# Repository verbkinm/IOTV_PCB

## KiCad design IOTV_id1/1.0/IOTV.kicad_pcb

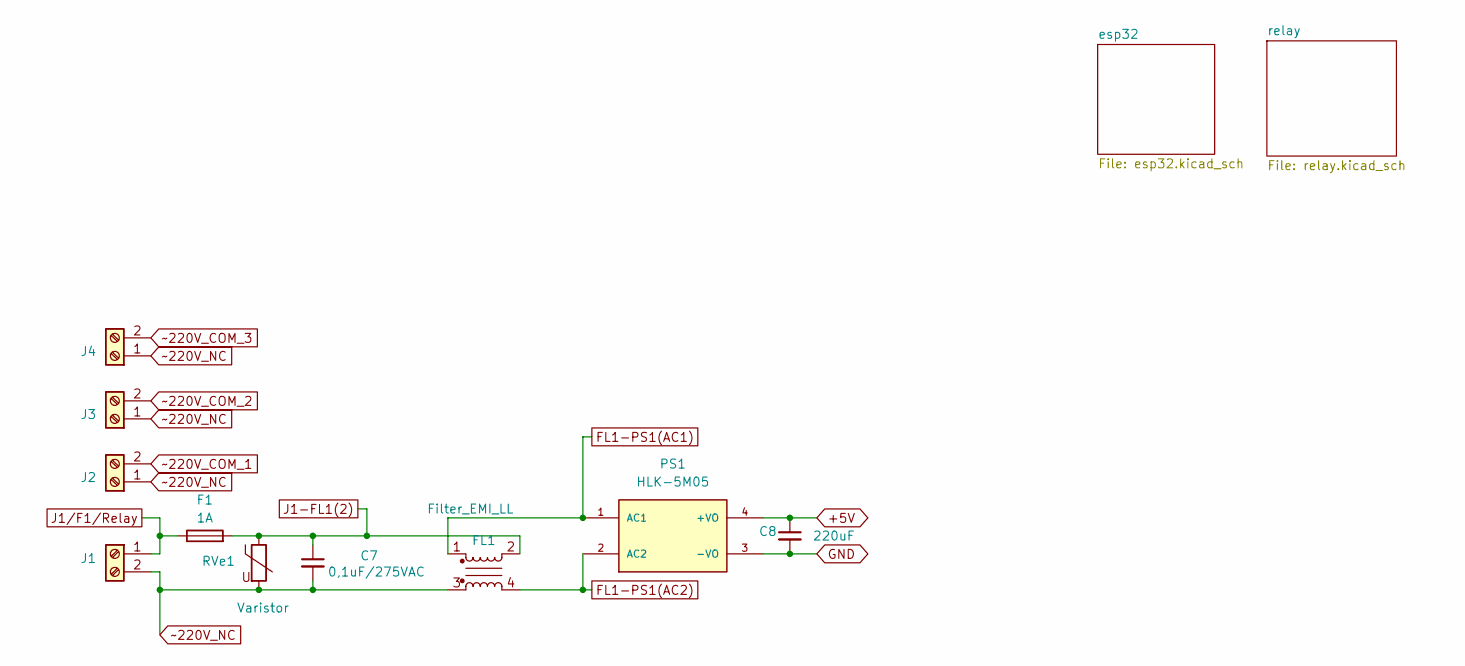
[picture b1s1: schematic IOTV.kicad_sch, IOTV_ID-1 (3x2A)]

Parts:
C7: C_Generic; C_Rect_L13.0mm_W5.0mm_P10.00mm_FKS3_FKP3_MKS4
C8: C_Generic; CP_Radial_D8.0mm_P5.00mm
F1: 1A; Fuseholder_Cylinder-5x20mm_Schurter_0031_8201_Horizontal_Op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
FL1: Filter_EMI_LL; L_CommonMode_Toroid_Vertical_10x13mm
J1, J2, J3, J4: Screw_Terminal_01x02; TerminalBlock_Phoenix_MKDS-1,5-2_1x02_P5.00mm_Horizontal
PS1: HLK-5M05; Converter_ACDC_Hi-Link_HLK-5Mxx; PARTREV N/A
RVe1: Varistor; RV_Disc_D21.5mm_W4.8mm_P10mm

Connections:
+5V: C8.1, PS1.4 (+VO); also elsewhere on the board
FL1-PS1(AC1): FL1.1, PS1.1 (AC1)
FL1-PS1(AC2): FL1.4, PS1.2 (AC2)
GND: C8.2, PS1.3 (-VO); also elsewhere on the board
J1-FL1(2): C7.1, F1.2, FL1.2, RVe1.1
J1/F1/Relay: F1.1, J1.1; also elsewhere on the board
~220V_COM_1: J2.2; also elsewhere on the board
~220V_COM_2: J3.2; also elsewhere on the board
~220V_COM_3: J4.2; also elsewhere on the board
~220V_NC: C7.2, FL1.3, J1.2, J2.1, J3.1, J4.1, RVe1.2

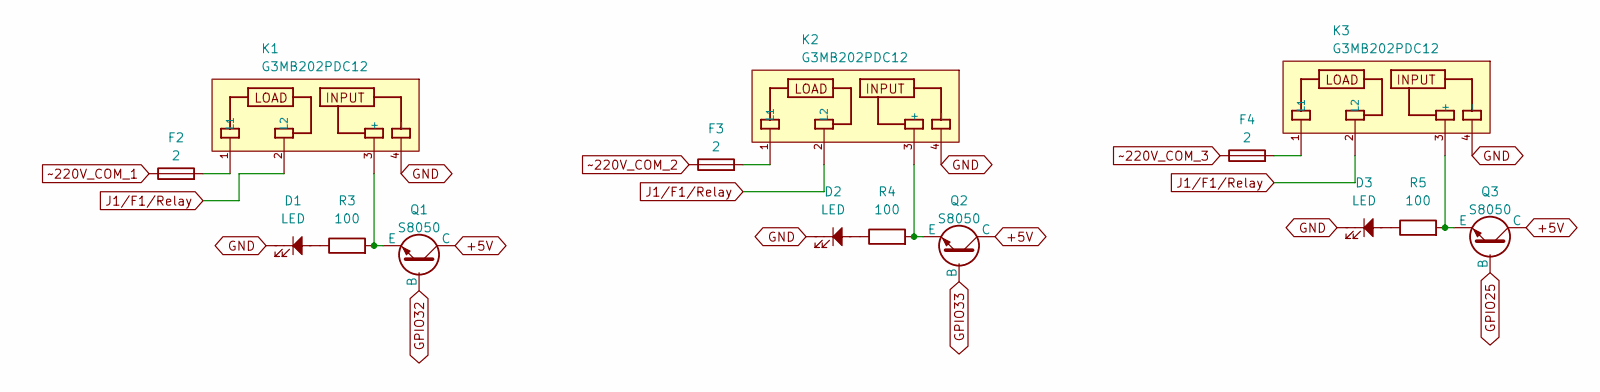
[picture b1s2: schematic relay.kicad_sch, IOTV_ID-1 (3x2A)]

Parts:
D1, D2, D3: LED; D_0603_1608Metric
F2, F3, F4: 2; Fuseholder_Cylinder-5x20mm_Schurter_0031_8201_Horizontal_Op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
K1, K2, K3: G3MB202PDC12; RELAY_G3MB202PDC12; PARTREV N/A
Q1, Q2, Q3: S8050; SOT-23
R3, R4, R5: 100; R_1206_3216Metric

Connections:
+5V: Q1.3 (C), Q2.3 (C), Q3.3 (C); also elsewhere on the board
GND: D1.1, D2.1, D3.1, K1.4 (-), K2.4 (-), K3.4 (-); also elsewhere on the board
GPIO25: Q3.1 (B); also elsewhere on the board
GPIO32: Q1.1 (B); also elsewhere on the board
GPIO33: Q2.1 (B); also elsewhere on the board
J1/F1/Relay: K1.2 (L2), K2.2 (L2), K3.2 (L2); also elsewhere on the board
unnamed: D1.2, R3.1
unnamed: D2.2, R4.1
unnamed: D3.2, R5.1
unnamed: K1.3 (+), Q1.2 (E), R3.2
unnamed: F2.2, K1.1 (L1)
unnamed: K2.3 (+), Q2.2 (E), R4.2
unnamed: F3.2, K2.1 (L1)
unnamed: K3.3 (+), Q3.2 (E), R5.2
unnamed: F4.2, K3.1 (L1)
~220V_COM_1: F2.1; also elsewhere on the board
~220V_COM_2: F3.1; also elsewhere on the board
~220V_COM_3: F4.1; also elsewhere on the board

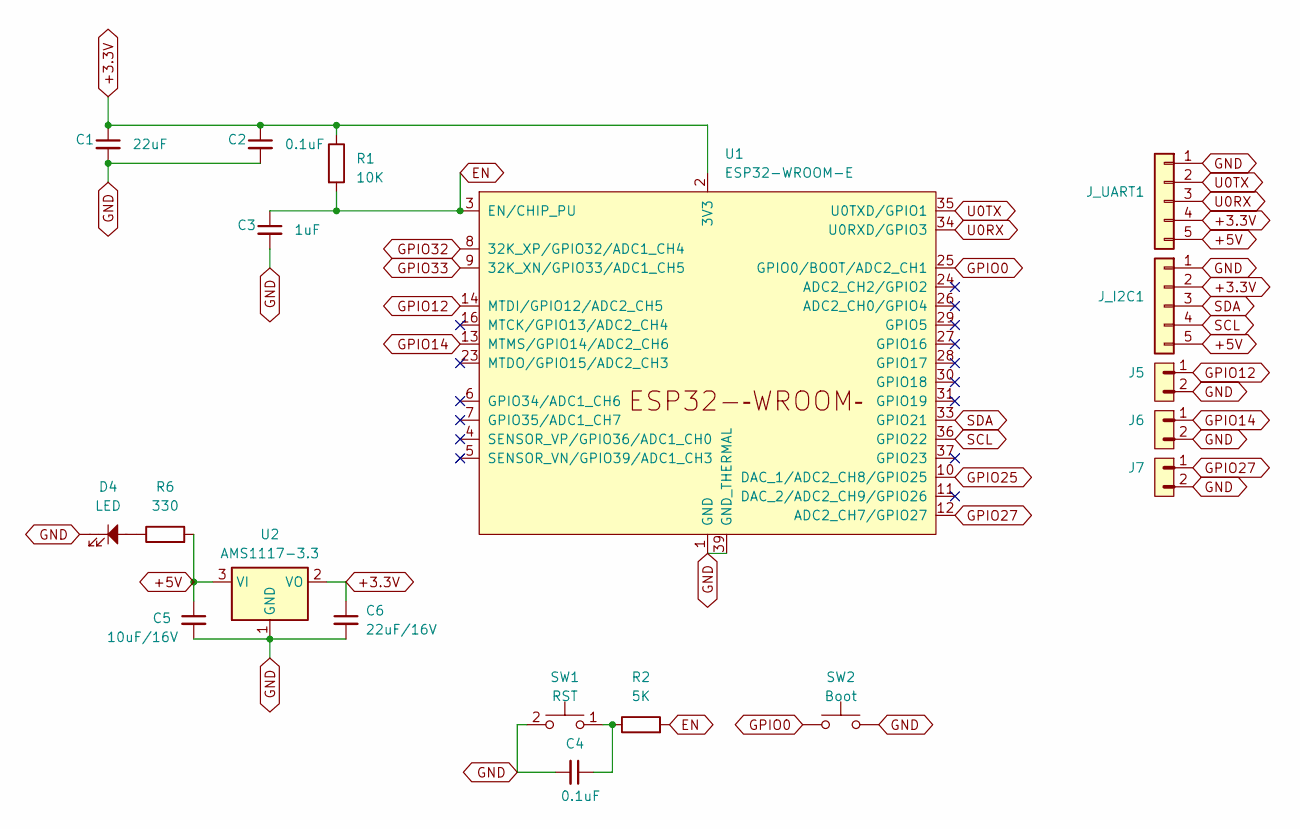
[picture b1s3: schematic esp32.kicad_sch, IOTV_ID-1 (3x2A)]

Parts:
C1, C2, C3, C4: C_Generic; C_1206_3216Metric
C5, C6: 10uF_0805_25V; C_1206_3216Metric; Part Number GRM21BR61E106MA73L; JLCPCB ID C15850
D4: LED; D_0603_1608Metric
J5, J6, J7: PINHD_1x2_Male; PinHeader_1x02_P2.54mm_Vertical
J_I2C1: Conn_01x05; PinHeader_1x05_P2.54mm_Vertical
J_UART1: Conn_01x05; PinHeader_1x05_P2.54mm_Vertical
R1: 10K; R_1206_3216Metric
R2: 5K; R_1206_3216Metric
R6: 330; R_1206_3216Metric
SW1: RST; SW_SPST_TL3342
SW2: Boot; SW_SPST_TL3342
U1: ESP32-WROOM-E; ESP32-WROOM-32E
U2: AMS1117-3.3; SOT-223-3_TabPin2

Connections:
+3.3V: C1.1, C2.1, C6.1, J_I2C1.2, J_UART1.4, R1.1, U1.2 (3V3), U2.2 (VO)
+5V: C5.1, J_I2C1.5, J_UART1.5, R6.2, U2.3 (VI); also elsewhere on the board
EN: C3.1, R1.2, R2.2, U1.3 (EN/CHIP_PU)
GND: C1.2, C2.2, C3.2, C4.2, C5.2, C6.2, D4.1, J5.2, J6.2, J7.2, J_I2C1.1, J_UART1.1, SW1.2, SW2.2, U1.1 (GND), U1.15 (GND), U1.38 (GND), U1.39 (GND_THERMAL), U2.1 (GND); also elsewhere on the board
GPIO0: SW2.1, U1.25 (GPIO0/BOOT/ADC2_CH1)
GPIO12: J5.1, U1.14 (MTDI/GPIO12/ADC2_CH5)
GPIO14: J6.1, U1.13 (MTMS/GPIO14/ADC2_CH6)
GPIO25: U1.10 (DAC_1/ADC2_CH8/GPIO25); also elsewhere on the board
GPIO27: J7.1, U1.12 (ADC2_CH7/GPIO27)
GPIO32: U1.8 (32K_XP/GPIO32/ADC1_CH4); also elsewhere on the board
GPIO33: U1.9 (32K_XN/GPIO33/ADC1_CH5); also elsewhere on the board
unnamed: C4.1, R2.1, SW1.1
unnamed: D4.2, R6.1
SCL: J_I2C1.4, U1.36 (GPIO22)
SDA: J_I2C1.3, U1.33 (GPIO21)
U0RX: J_UART1.3, U1.34 (U0RXD/GPIO3)
U0TX: J_UART1.2, U1.35 (U0TXD/GPIO1)

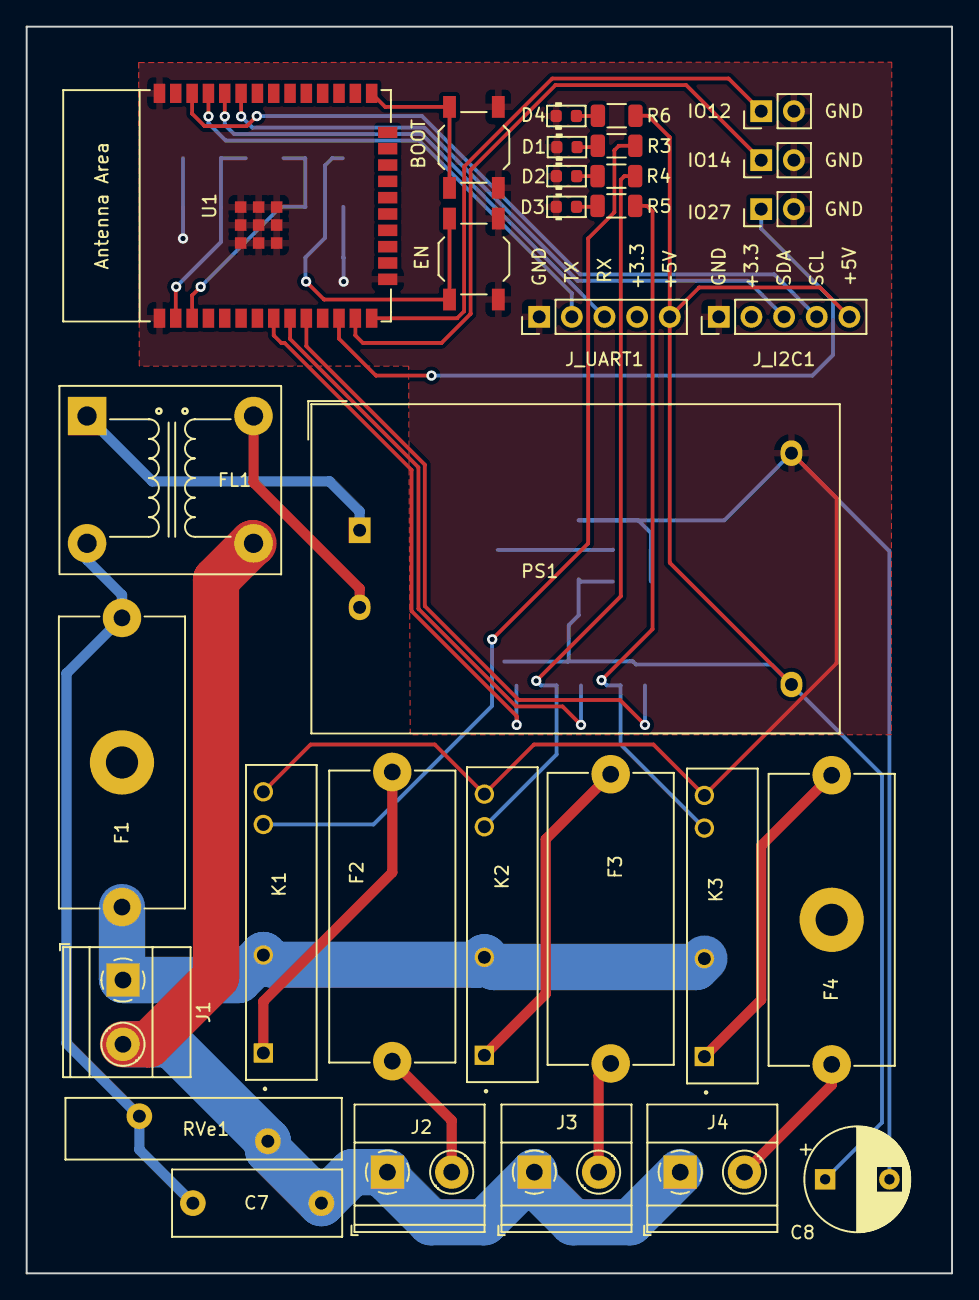
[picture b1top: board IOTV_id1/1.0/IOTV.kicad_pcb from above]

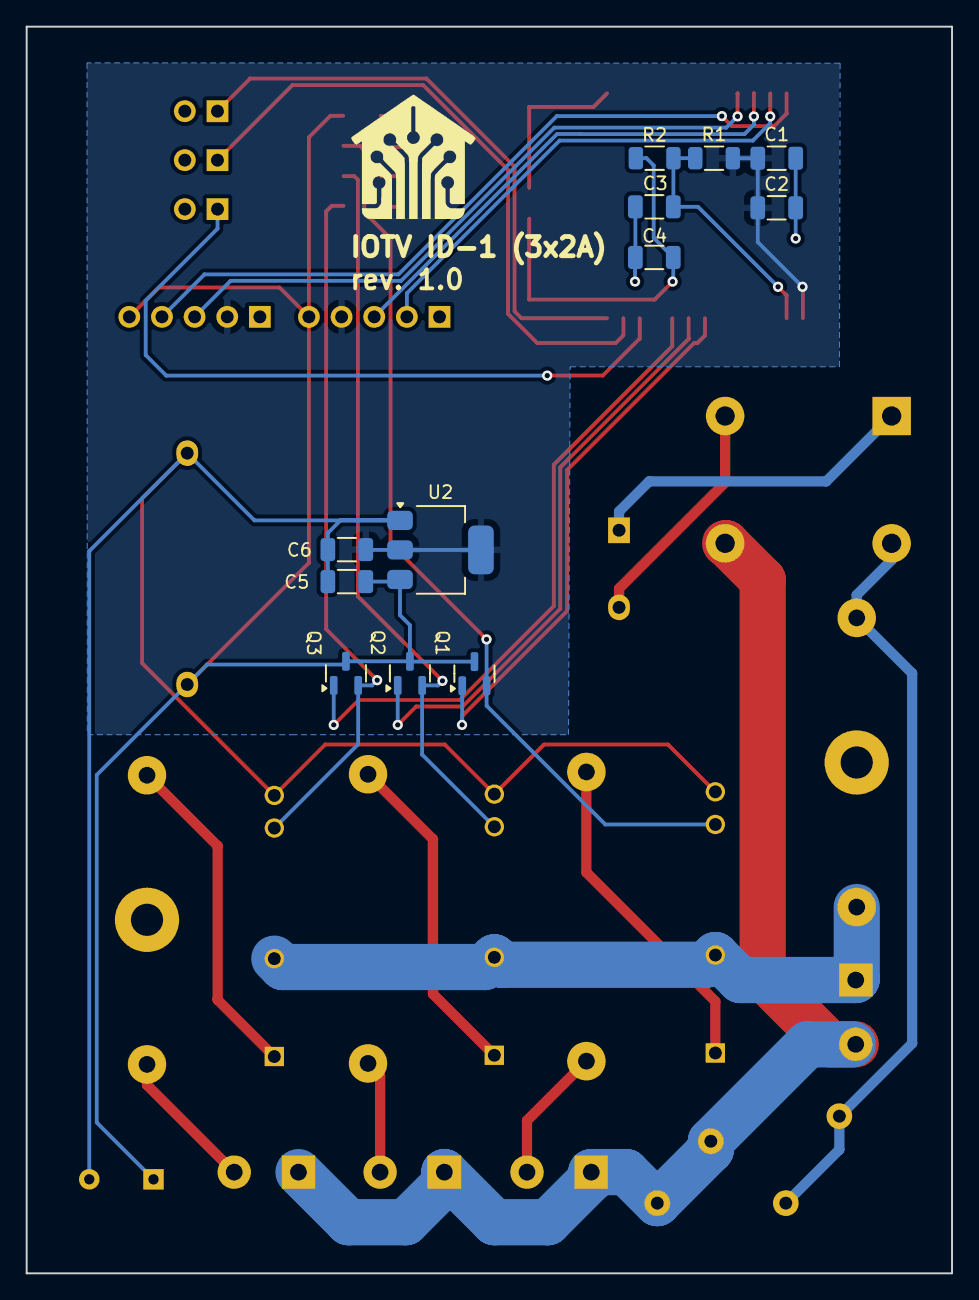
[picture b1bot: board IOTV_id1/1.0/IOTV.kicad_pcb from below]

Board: 2 copper layers, 72.0 x 97.0 mm, 44 parts (12 on the bottom side), 34 nets.

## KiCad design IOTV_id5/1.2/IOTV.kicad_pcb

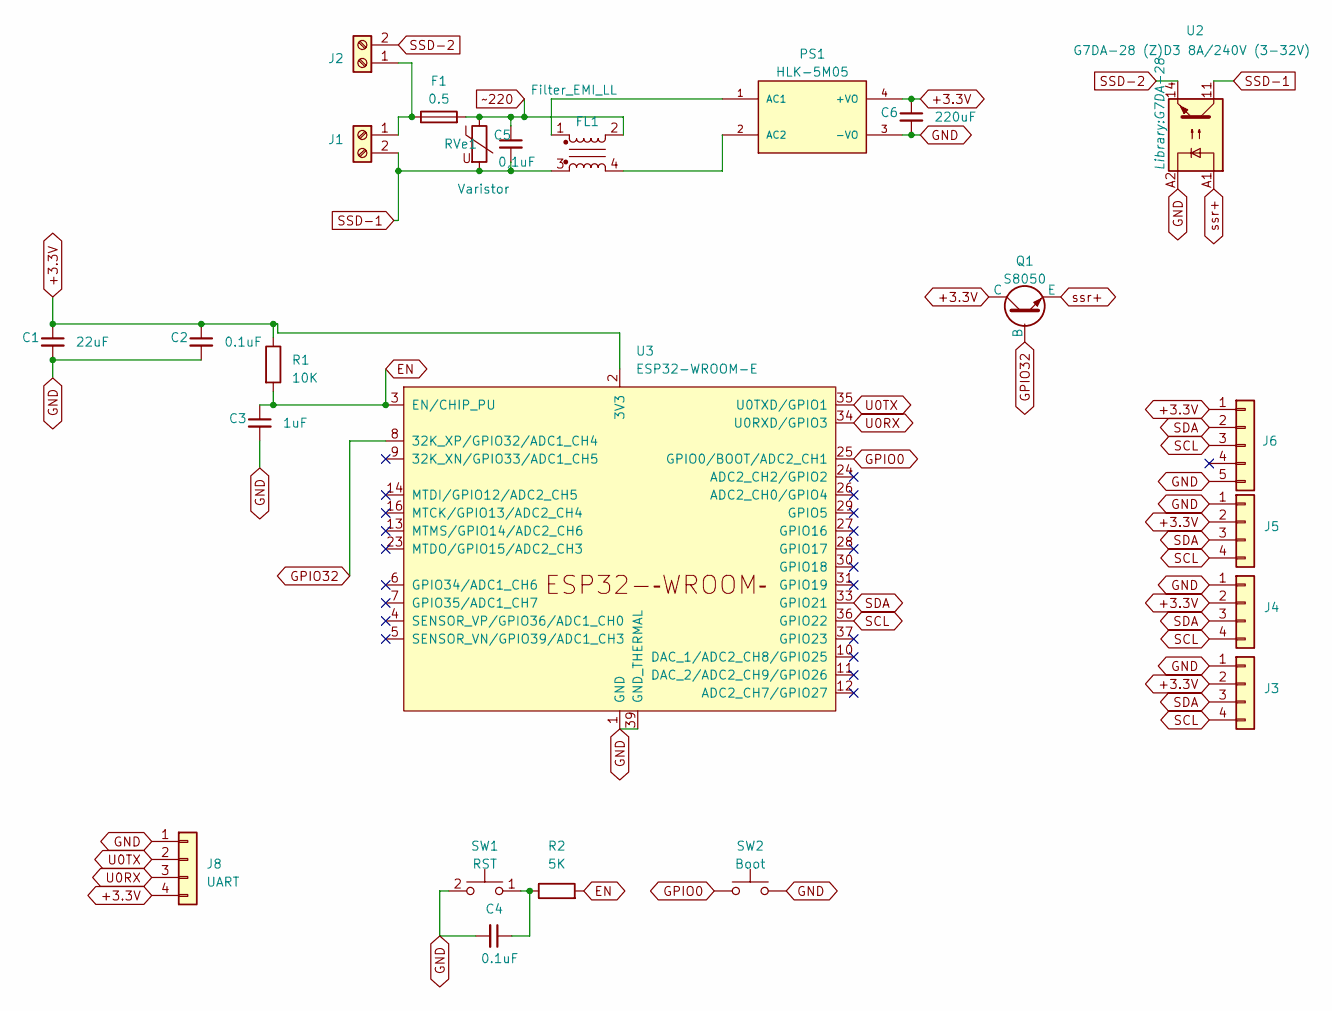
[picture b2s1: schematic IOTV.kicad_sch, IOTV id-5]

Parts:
C1, C2, C3, C4: C_Generic; C_1206_3216Metric
C5: C_Generic; C_Rect_L13.0mm_W5.0mm_P10.00mm_FKS3_FKP3_MKS4
C6: C_Generic; CP_Radial_D8.0mm_P5.00mm
F1: 0.5; Fuseholder_Cylinder-5x20mm_Schurter_0031_8201_Horizontal_Op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
FL1: Filter_EMI_LL; L_CommonMode_Toroid_Vertical_10x13mm
J1, J2: Screw_Terminal_01x02; TerminalBlock_Phoenix_MKDS-1,5-2_1x02_P5.00mm_Horizontal
J3, J4, J5: Conn_01x04; PinHeader_1x04_P2.54mm_Vertical
J6: Conn_01x05; PinHeader_1x05_P2.54mm_Vertical
J8: UART; PinHeader_1x04_P2.54mm_Vertical
PS1: HLK-5M05; CONV_HLK-5M05; PARTREV N/A
Q1: S8050; SOT-23
R1: 10K; R_1206_3216Metric
R2: 5K; R_1206_3216Metric
RVe1: Varistor; RV_Disc_D21.5mm_W4.8mm_P10mm
SW1: RST; SW_SPST_TL3342
SW2: Boot; SW_SPST_TL3342
U2: G7DA-28 (Z)D3 8A/240V (3-32V); G7DA-28
U3: ESP32-WROOM-E; ESP32-WROOM-32E

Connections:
+3.3V: C1.1, C2.1, C6.1, J3.2, J4.2, J5.2, J6.1, J8.4, PS1.4 (+VO), Q1.3 (C), R1.1, U3.2 (3V3)
EN: C3.1, R1.2, R2.2, U3.3 (EN/CHIP_PU)
GND: C1.2, C2.2, C3.2, C4.2, C6.2, J3.1, J4.1, J5.1, J6.5, J8.1, PS1.3 (-VO), SW1.2, SW2.2, U2.A2, U3.1 (GND), U3.15 (GND), U3.38 (GND), U3.39 (GND_THERMAL)
GPIO0: SW2.1, U3.25 (GPIO0/BOOT/ADC2_CH1)
GPIO32: Q1.1 (B), U3.8 (32K_XP/GPIO32/ADC1_CH4)
unnamed: C4.1, R2.1, SW1.1
unnamed: F1.1, J1.1, J2.1
unnamed: FL1.1, PS1.1 (AC1)
unnamed: FL1.4, PS1.2 (AC2)
SCL: J3.4, J4.4, J5.4, J6.3, U3.36 (GPIO22)
SDA: J3.3, J4.3, J5.3, J6.2, U3.33 (GPIO21)
SSD-1: C5.2, FL1.3, J1.2, RVe1.2, U2.11
SSD-2: J2.2, U2.14
U0RX: J8.3, U3.34 (U0RXD/GPIO3)
U0TX: J8.2, U3.35 (U0TXD/GPIO1)
ssr+: Q1.2 (E), U2.A1
~220: C5.1, F1.2, FL1.2, RVe1.1

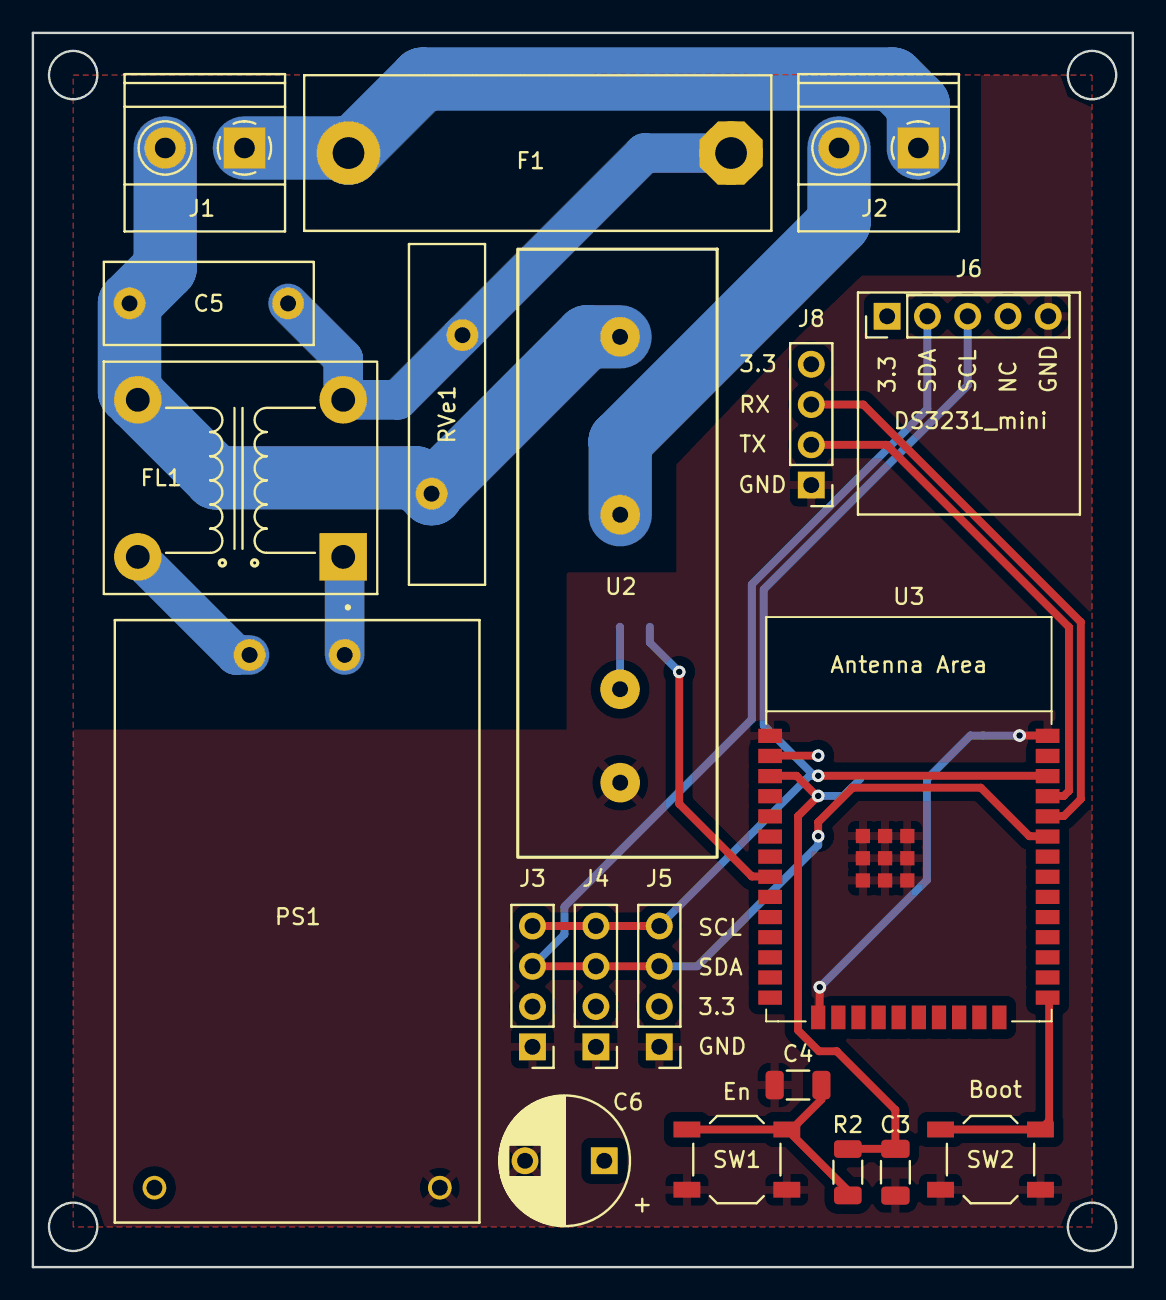
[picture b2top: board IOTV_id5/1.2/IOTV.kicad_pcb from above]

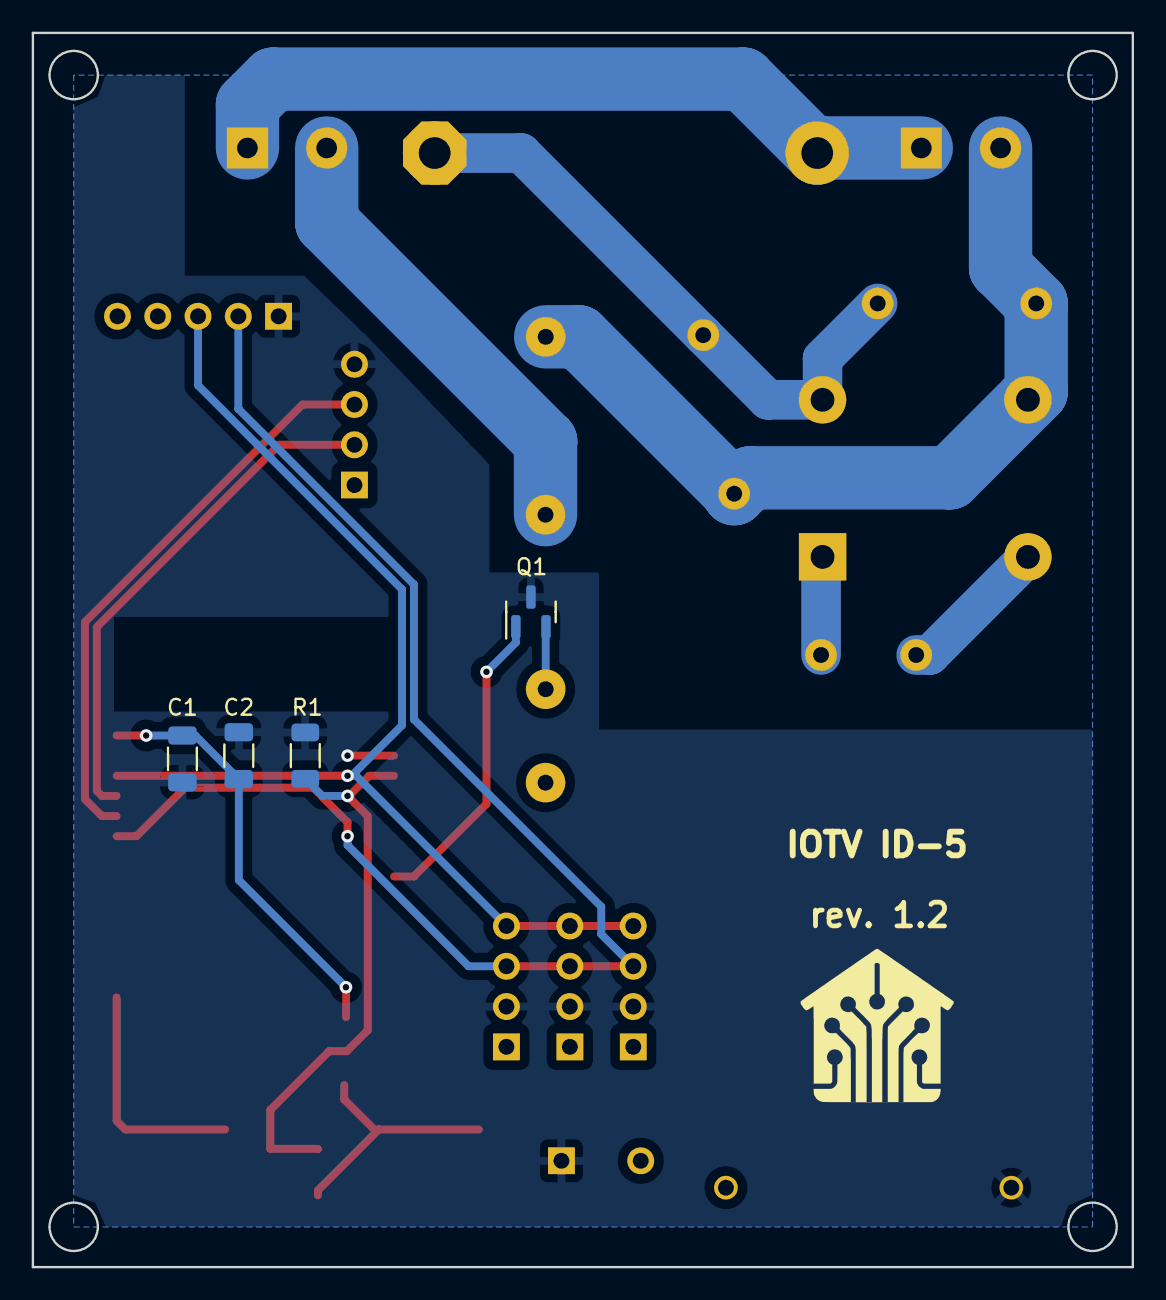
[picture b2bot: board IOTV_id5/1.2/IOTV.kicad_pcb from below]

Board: 2 copper layers, 69.4 x 77.8 mm, 24 parts (4 on the bottom side), 17 nets.

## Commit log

2024-07-25 id_1 1.0
2024-07-29 id1 1.0
2024-07-30 id1 (3x2A) 1.0
    Проверка резонит.
2024-07-30 id1 (3x2A) 1.0
    png файлы
2024-07-31 docs +
